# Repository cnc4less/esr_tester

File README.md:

# Tester dei condensatori

Questo strumento consente di trovare i condensatori guasti senza 
toglierli dalla scheda elettronica.
Alimentazione 9 Volt.

Il progetto fu pubblicato su Nuova Elettronica.
	
Si tratta di progettare il PCB per poterlo fare stampare in 10+ copie.

Una stima dei costi si trova in `source/prezzi.ods`.

I file che dobbiamo dare alla fabbrica saranno in formato Gerber.

ESR significa resistenza equivalente in serie di un condensatore

## Software utilizzato

+ KiCad per la progettazione elettronica.
+ LibreOffice per i fogli di calcolo (Formato OpenDocument, estensione `ods`).
+ Git per il controllo delle versioni.

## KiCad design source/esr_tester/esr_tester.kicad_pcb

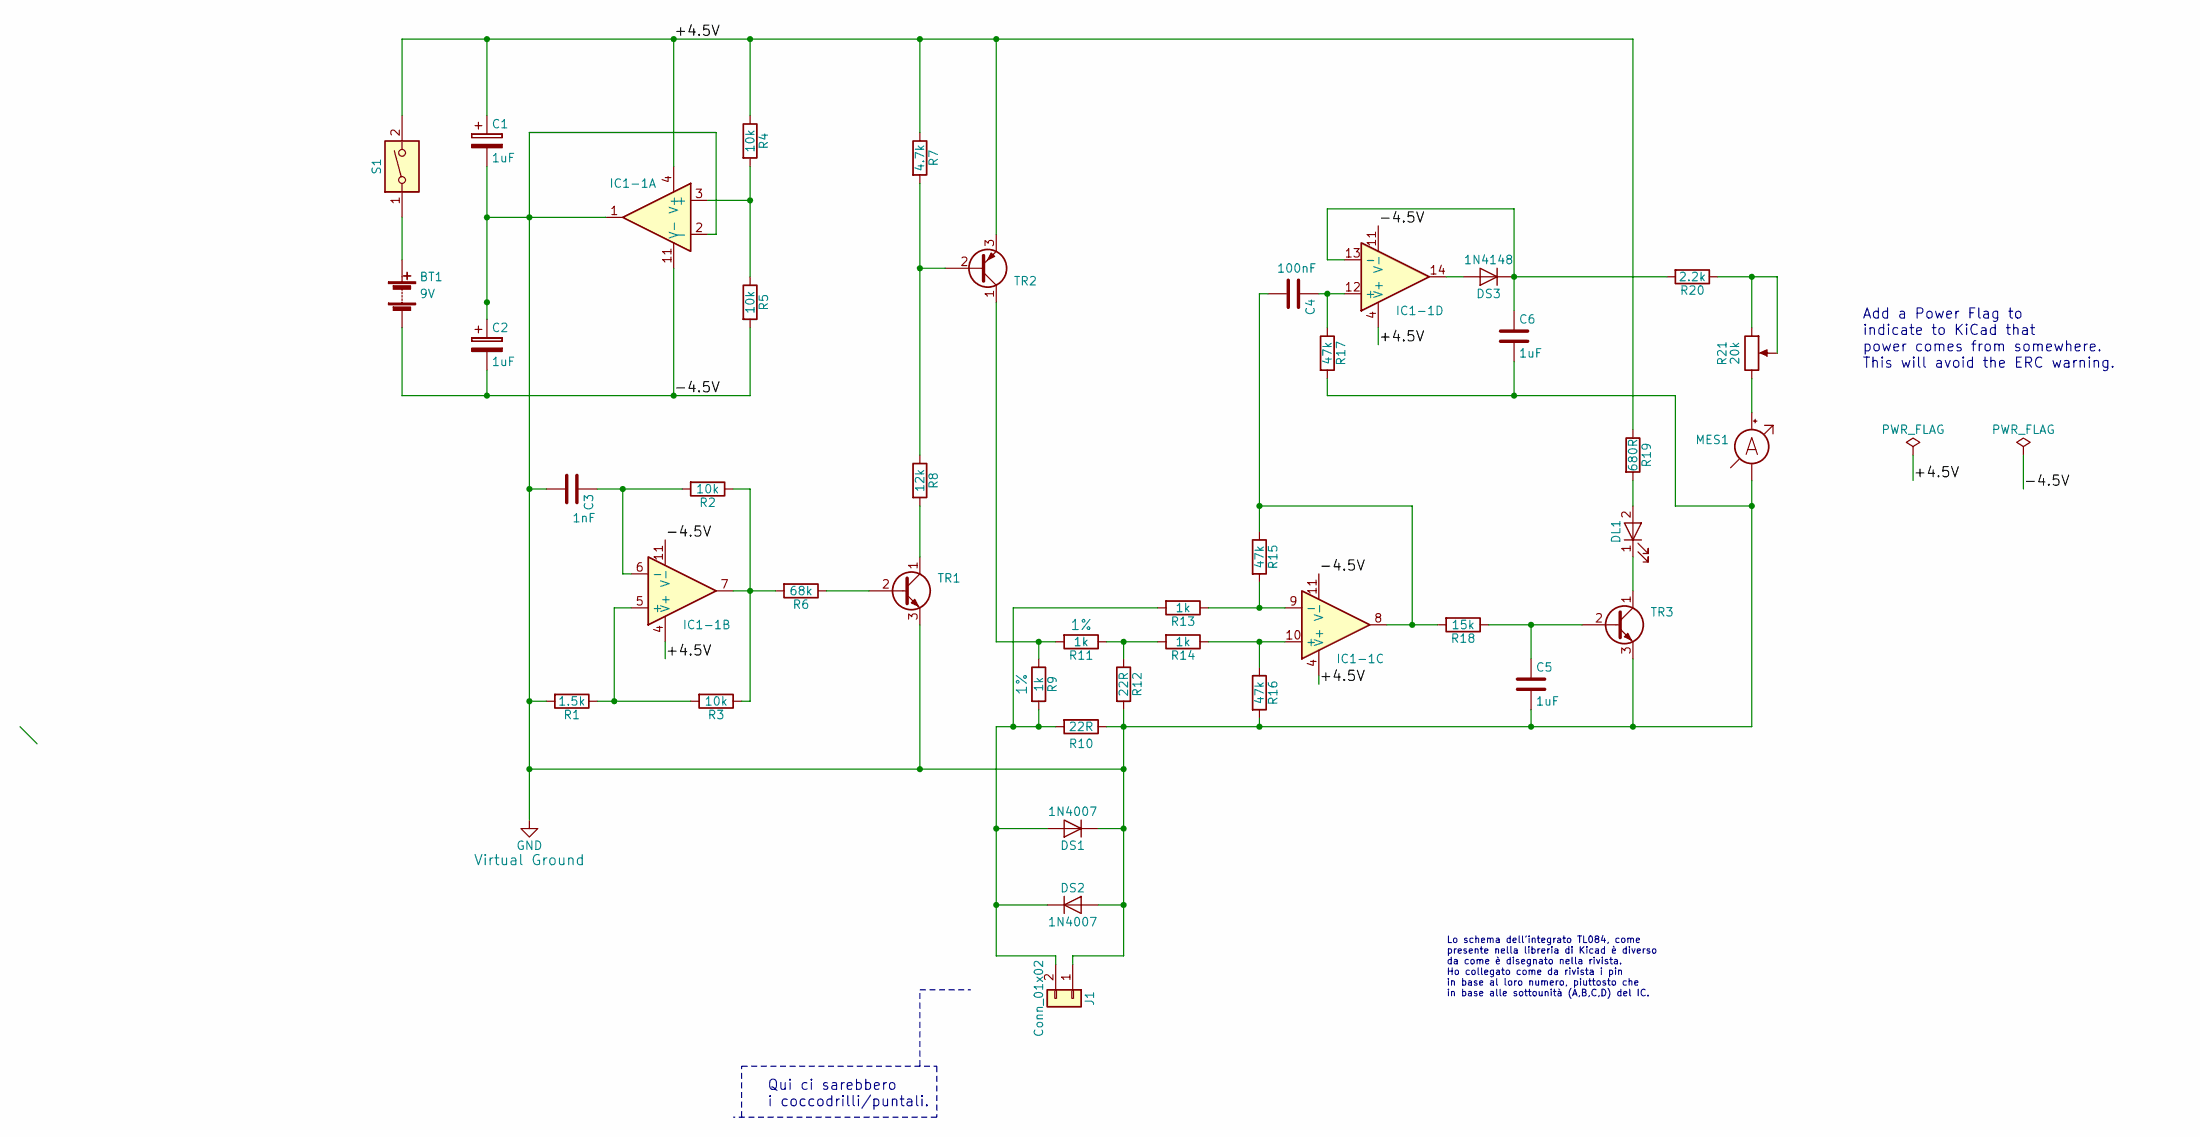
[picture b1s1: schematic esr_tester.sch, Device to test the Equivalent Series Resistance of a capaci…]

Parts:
BT1: 9V; Socket_Strip_Straight_1x02_Pitch2.54mm
C1, C2: 1uF; CP_Radial_D5.0mm_P2.50mm
C3: 1nF; C_Rect_L7.0mm_W2.5mm_P5.00mm
C4: 100nF; C_Rect_L7.0mm_W2.5mm_P5.00mm
C5, C6: 1uF; C_Rect_L7.0mm_W4.5mm_P5.00mm
DL1: LED; LED_D3.0mm
DS1, DS2: 1N4007; D_DO-35_SOD27_P2.54mm_Vertical_KathodeUp
DS3: 1N4148; D_DO-35_SOD27_P2.54mm_Vertical_KathodeUp
IC1-1: TL084; DIP-14_W7.62mm
J1: Conn_01x02; Socket_Strip_Straight_1x02_Pitch2.54mm
MES1: Amperemeter_DC; Socket_Strip_Straight_1x02_Pitch2.54mm
R1: 1.5k; R_Axial_DIN0207_L6.3mm_D2.5mm_P2.54mm_Vertical
R2, R3, R4, R5: 10k; R_Axial_DIN0207_L6.3mm_D2.5mm_P2.54mm_Vertical
R6: 68k; R_Axial_DIN0207_L6.3mm_D2.5mm_P2.54mm_Vertical
R7: 4.7k; R_Axial_DIN0207_L6.3mm_D2.5mm_P2.54mm_Vertical
R8: 12k; R_Axial_DIN0207_L6.3mm_D2.5mm_P2.54mm_Vertical
R9, R11: 1k; R_Axial_DIN0207_L6.3mm_D2.5mm_P2.54mm_Vertical; Tolerance 1%
R10, R12: 22R; R_Axial_DIN0207_L6.3mm_D2.5mm_P2.54mm_Vertical
R13, R14: 1k; R_Axial_DIN0207_L6.3mm_D2.5mm_P2.54mm_Vertical
R15, R16, R17: 47k; R_Axial_DIN0207_L6.3mm_D2.5mm_P2.54mm_Vertical
R18: 15k; R_Axial_DIN0207_L6.3mm_D2.5mm_P2.54mm_Vertical
R19: 680R; R_Axial_DIN0207_L6.3mm_D2.5mm_P2.54mm_Vertical
R20: 2.2k; R_Axial_DIN0207_L6.3mm_D2.5mm_P2.54mm_Vertical
R21: 20k; Potentiometer_Trimmer_Bourns_3266Y
S1: interruttore; Socket_Strip_Straight_1x03_Pitch2.54mm
TR1, TR3: BC547; TO-92_Inline_Wide
TR2: BC557; TO-92_Inline_Wide

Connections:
/+4.5V: C1.1, IC1-1.4 (V+), R4.1, R7.1, R19.1, S1.2, TR2.3 (E)
/-4.5V: BT1.2 (-), C2.2, IC1-1.11 (V-), R5.2
GND: C1.2, C2.1, C3.2, C5.2, C6.2, DS1.1 (K), DS2.2 (A), IC1-1.1, IC1-1.2 (-), J1.1, MES1.1 (-), R1.2, R10.1, R12.2, R16.2, R17.2, TR1.3 (E), TR3.3 (E)
unnamed: BT1.1 (+), S1.1
unnamed: C3.1, IC1-1.6 (-), R2.2
unnamed: C4.1, IC1-1.12 (+), R17.1
unnamed: C4.2, IC1-1.8, R15.1, R18.2
unnamed: C5.1, R18.1, TR3.2 (B)
unnamed: C6.1, DS3.1 (K), IC1-1.13 (-), R20.2
unnamed: DL1.1 (K), TR3.1 (C)
unnamed: DL1.2 (A), R19.2
unnamed: DS1.2 (A), DS2.1 (K), J1.2, R9.2, R10.2, R13.2
unnamed: DS3.2 (A), IC1-1.14
unnamed: IC1-1.3 (+), R4.2, R5.1
unnamed: IC1-1.5 (+), R1.1, R3.2
unnamed: IC1-1.7, R2.1, R3.1, R6.2
unnamed: IC1-1.9 (-), R13.1, R15.2
unnamed: IC1-1.10 (+), R14.1, R16.1
unnamed: MES1.2 (+), R21.3
unnamed: R6.1, TR1.2 (B)
unnamed: R7.2, R8.1, TR2.2 (B)
unnamed: R8.2, TR1.1 (C)
unnamed: R11.1, R12.1, R14.2
unnamed: R9.1, R11.2, TR2.1 (C)
unnamed: R20.1, R21.1, R21.2

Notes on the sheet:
Qui ci sarebbero i coccodrilli/puntali.
Lo schema dell'integrato TL084, come presente nella libreria di Kicad è diverso da come è disegnato nella rivista. Ho collegato come da rivista i pin in base al loro numero, piuttosto che in base alle sottounità (A,B,C,D) del IC.
Add a Power Flag to indicate to KiCad that power comes from somewhere. This will avoid the ERC warning.

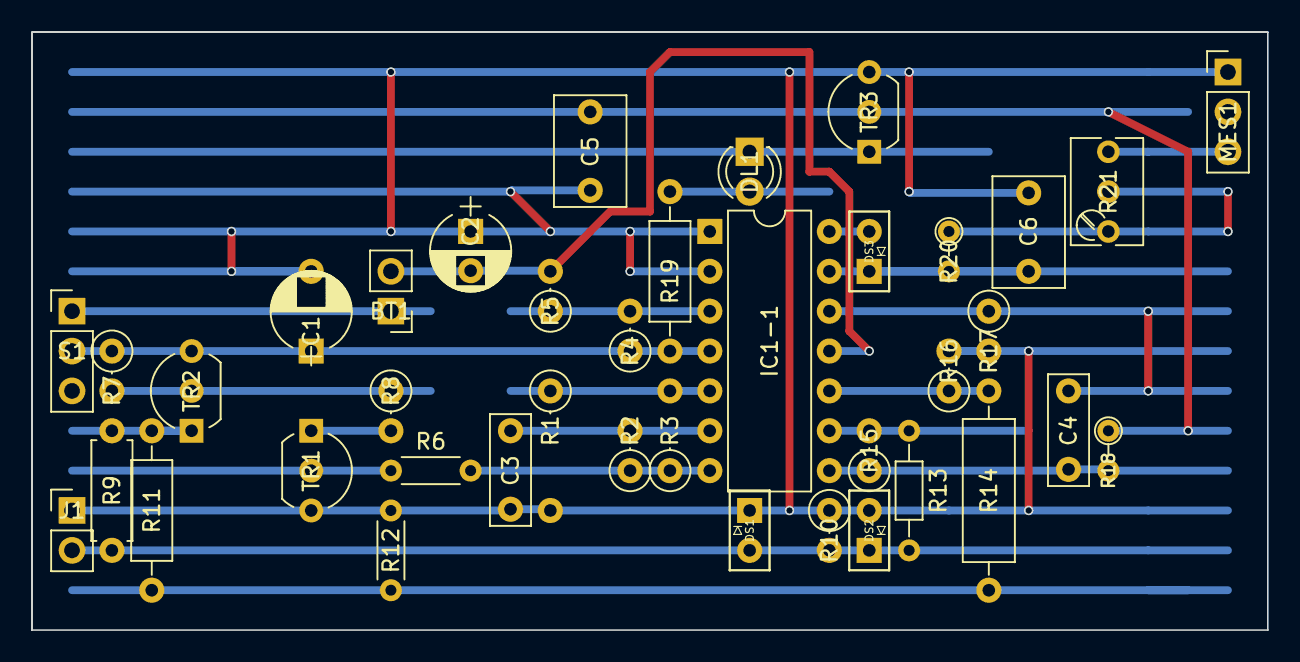
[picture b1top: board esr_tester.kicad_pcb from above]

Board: 2 copper layers, 78.7 x 38.1 mm, 39 parts (0 on the bottom side), 25 nets.

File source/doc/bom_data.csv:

1,"S1","interruttore","Buttons_Switches_THT:SW_PUSH-12mm",,
2,"C1","1uF","Capacitors_THT:CP_Radial_D5.0mm_P2.50mm",,
3,"C2","1uF","Capacitors_THT:CP_Radial_D5.0mm_P2.50mm",,
4,"IC1-1","TL084","Housings_DIP:DIP-14_W7.62mm",,
5,"R4","10k","Resistors_THT:R_Axial_DIN0204_L3.6mm_D1.6mm_P5.08mm_Horizontal",,
6,"R5","10k","Resistors_THT:R_Axial_DIN0204_L3.6mm_D1.6mm_P5.08mm_Horizontal",,
7,"C3","1nF","Capacitors_THT:C_Disc_D3.0mm_W1.6mm_P2.50mm","Polyester",
8,"R1","1.5k","Resistors_THT:R_Axial_DIN0204_L3.6mm_D1.6mm_P5.08mm_Horizontal",,
9,"R2","10k","Resistors_THT:R_Axial_DIN0204_L3.6mm_D1.6mm_P5.08mm_Horizontal",,
10,"R3","10k","Resistors_THT:R_Axial_DIN0204_L3.6mm_D1.6mm_P5.08mm_Horizontal",,
11,"R6","68k","Resistors_THT:R_Axial_DIN0204_L3.6mm_D1.6mm_P5.08mm_Horizontal",,
12,"TR1","BC547","TO_SOT_Packages_THT:TO-92_Molded_Narrow",,
13,"TR2","BC557","TO_SOT_Packages_THT:TO-92_Molded_Narrow",,
14,"R8","12k","Resistors_THT:R_Axial_DIN0204_L3.6mm_D1.6mm_P5.08mm_Horizontal",,
15,"R7","4.7k","Resistors_THT:R_Axial_DIN0204_L3.6mm_D1.6mm_P5.08mm_Horizontal",,
16,"R9","1k","Resistors_THT:R_Axial_DIN0204_L3.6mm_D1.6mm_P5.08mm_Horizontal",,"1%"
17,"R12","22R","Resistors_THT:R_Axial_DIN0204_L3.6mm_D1.6mm_P5.08mm_Horizontal",,
18,"R10","22R","Resistors_THT:R_Axial_DIN0204_L3.6mm_D1.6mm_P5.08mm_Horizontal",,
19,"R11","1k","Resistors_THT:R_Axial_DIN0204_L3.6mm_D1.6mm_P5.08mm_Horizontal",,"1%"
20,"R13","1k","Resistors_THT:R_Axial_DIN0204_L3.6mm_D1.6mm_P5.08mm_Horizontal",,
21,"R14","1k","Resistors_THT:R_Axial_DIN0204_L3.6mm_D1.6mm_P5.08mm_Horizontal",,
22,"R16","47k","Resistors_THT:R_Axial_DIN0204_L3.6mm_D1.6mm_P5.08mm_Horizontal",,
23,"R15","47k","Resistors_THT:R_Axial_DIN0204_L3.6mm_D1.6mm_P5.08mm_Horizontal",,
24,"R18","15k","Resistors_THT:R_Axial_DIN0204_L3.6mm_D1.6mm_P5.08mm_Horizontal",,
25,"C5","1uF","Capacitors_THT:C_Disc_D3.0mm_W1.6mm_P2.50mm","Polyester",
26,"TR3","BC547","TO_SOT_Packages_THT:TO-92_Molded_Narrow",,
27,"DL1","LED","LEDs:LED_D3.0mm",,
28,"R19","680R","Resistors_THT:R_Axial_DIN0204_L3.6mm_D1.6mm_P5.08mm_Horizontal",,
29,"C4","100nF","Capacitors_THT:C_Disc_D3.0mm_W1.6mm_P2.50mm","Polyester",
30,"R17","47k","Resistors_THT:R_Axial_DIN0204_L3.6mm_D1.6mm_P5.08mm_Horizontal",,
31,"DS3","1N4148","Diodes_THT:D_5W_P5.08mm_Vertical_AnodeUp",,
32,"C6","1uF","Capacitors_THT:C_Disc_D3.0mm_W1.6mm_P2.50mm","Polyester",
33,"R20","2.2k","Resistors_THT:R_Axial_DIN0204_L3.6mm_D1.6mm_P5.08mm_Horizontal",,
34,"R21","20k","Potentiometers:Potentiometer_Trimmer_ACP_CA9v_Horizontal_Px10.0mm_Py5.0mm",,
35,"MES1","Amperemeter_DC","Connectors:Banana_Jack_2Pin",,
36,"DS1","1N4007","Diodes_THT:D_5W_P5.08mm_Vertical_AnodeUp",,
37,"DS2","1N4007","Diodes_THT:D_5W_P5.08mm_Vertical_AnodeUp",,
38,"J1","Conn_01x01","Connectors:Banana_Jack_1Pin",,
39,"J2","Conn_01x01","Connectors:Banana_Jack_1Pin",,
40,"BT1","9V","Pin_Headers:Pin_Header_Straight_1x02_Pitch2.54mm",,

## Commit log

2017-10-12 Summary of what we already have
2017-10-15 Draw the electrical diagram `esr_tester.sch`. There are may things to check, as written on the diagram itself.
2017-10-15 Improve README.md
2017-10-23 update .gitignore with filters for kicad files
2017-10-23 fix schematic, add *cache.lib file
    - made visible components values
    - fixed C3 value
    - other small changes
2017-10-23 schematic annotation
2017-10-24 add netlist
2017-10-24 footprint association (schematics and netlist)
2017-12-10 Add a special «Power Flag» to indicate to KiCad that power comes from somewhere. This will avoid ERC warning.
2017-12-10 Modify schematics sheet properties, adding a title and company. Regenerate Netlist.
2017-12-10 Magazine and datasheet now are in «doc» directory. renamed: source/rivista/212_Nuova_Elettronica.pdf -> source/doc/212_Nuova_Elettronica.pdf renamed: source/rivista/articolo.pdf -> source/doc/articol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
2017-12-10 To generate a Bill of Materials (BOM), Kicad needs a plugin. Install XSLT processor `xsltproc` from your package manager or any other mean. Get a XSLT stylesheet. Copy `bom2csv.xsl` from Kicad instal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
    Generate the BOM as a comma-separated-values file.
    new file: source/esr_tester/esr_tester.csv
    new file: source/esr_tester/esr_tester.xml
2017-12-10 Work with tabular data with CSV and Sqlite3. modified: source/esr_tester/esr_tester.csv
    new file: source/doc/bom_data.csv
    Data definition.
    new file: source/doc/ddl.sql
    The database file.
    new file: source/doc/esr_db.sqlite
    The query output file.
2017-12-11 Import netlist into Pcbnew.
    Arrange footprints as in the magazine article.
    Draw a board edge.
2017-12-11 The branch proto2 is for a prototype build with stripboard.
    Schematics: changed connector for testing probes (one connector with
    two poles instead of two with one each).
    CvPcb: Changed some connectors, resistors and diodes footprints.
    Pcbnew: A new layout for a stripboard.
2017-12-15 Modify «.gitignore».
2017-12-15 Create a footprint library useful for stripboards.
    Modify layout to increase distance between not connected tracks
    on Bottom copper layer. This is needed to cleanly cut stripboard tracks.
    Plot on a SVG file (for printing). All layesr on one file.
